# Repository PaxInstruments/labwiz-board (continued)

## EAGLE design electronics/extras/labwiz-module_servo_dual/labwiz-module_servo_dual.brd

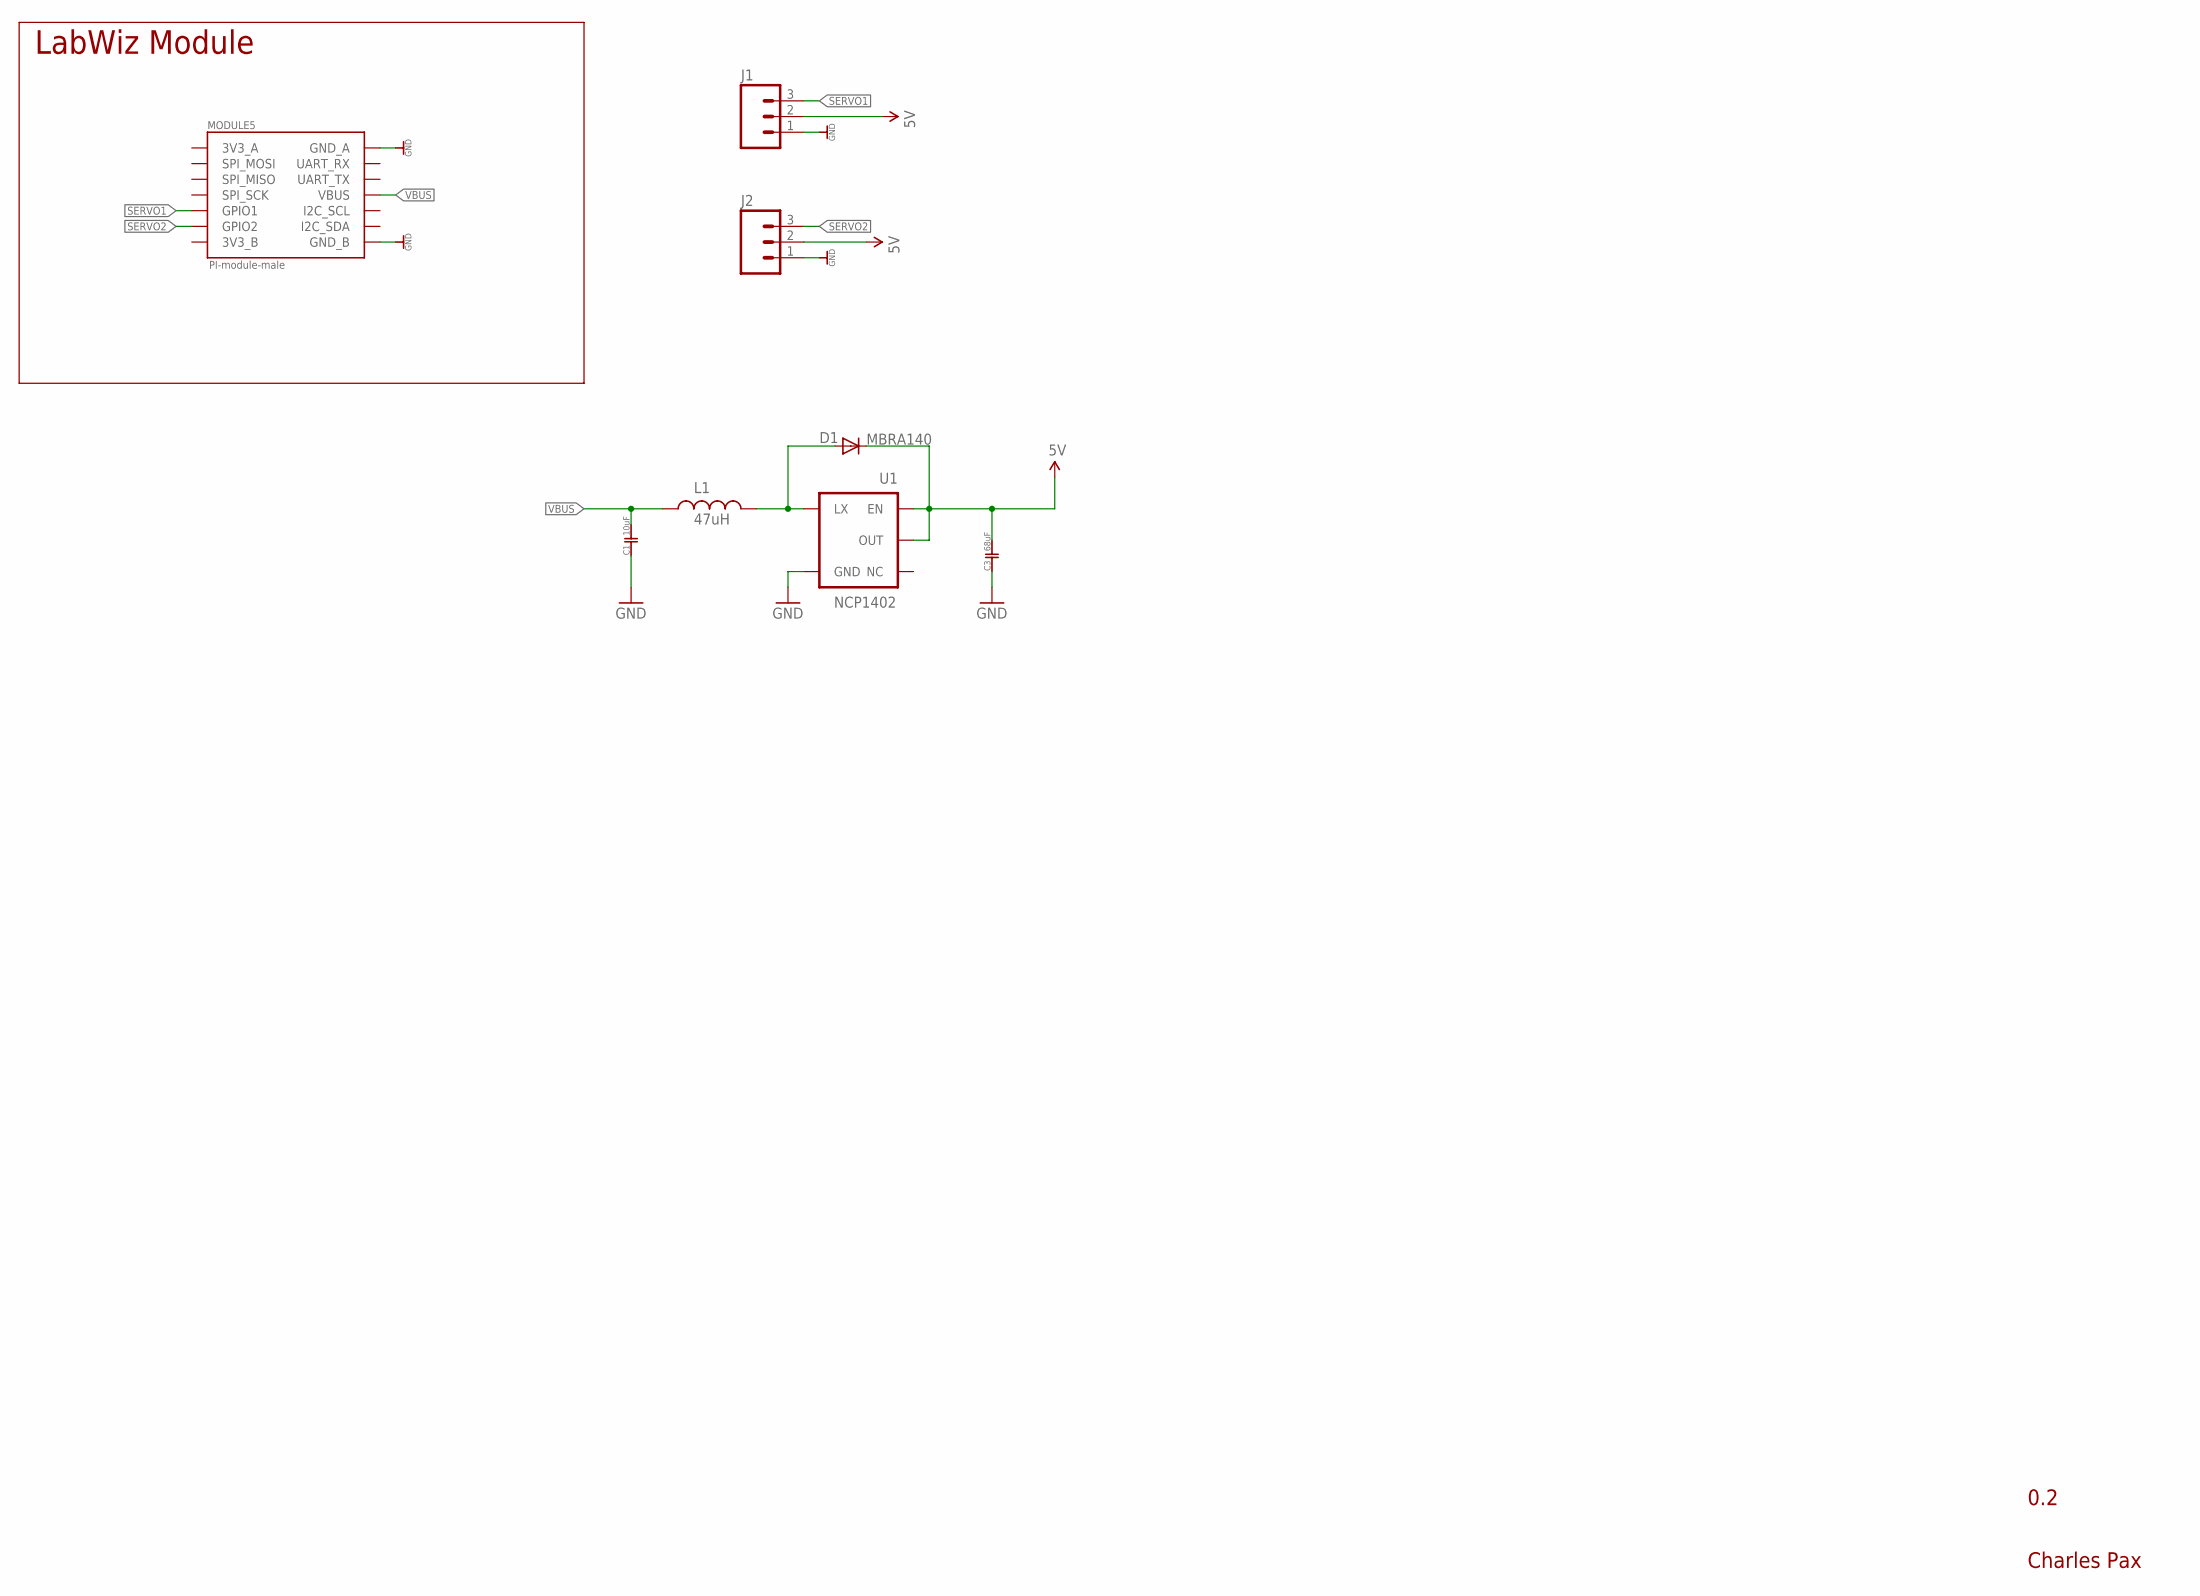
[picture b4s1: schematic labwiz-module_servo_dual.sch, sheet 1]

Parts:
C1: 10uF; 0603
C3: 68uF; 0603
D1: MBRA140; SMA-DIODE
J1, J2: M031X03_SMD_RA_MALE_POST_SMALLEST; 1X03_SMD_RA_MALE_POST_SMALLEST
L1: 47uH; CR54
MODULE5: PI-module-male; M07X2_2MM_EDGE
U1: NCP1402; SOT23-5

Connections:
3V3_A: MODULE5.P$13 (3V3_A)
5V: C3.2, D1.C, J1.2, J2.2, U1.1 (EN), U1.2 (OUT)
GND: C1.1, C3.1, J1.1, J2.1, MODULE5.P$2 (GND_B), MODULE5.P$14 (GND_A), U1.4 (GND)
unnamed: D1.A, L1.P$2 (2), U1.5 (LX)
SERVO1: J1.3, MODULE5.P$5 (GPIO1)
SERVO2: J2.3, MODULE5.P$3 (GPIO2)
VBUS: C1.2, L1.P$1 (1), MODULE5.P$8 (VBUS)

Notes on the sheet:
0.2
Charles Pax
LabWiz Module

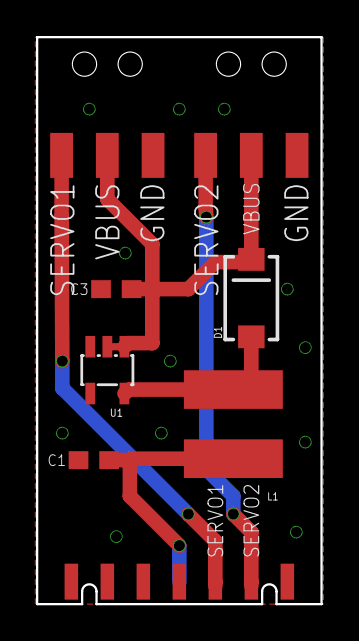
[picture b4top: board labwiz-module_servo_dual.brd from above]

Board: 4 copper layers, 15.8 x 31.5 mm, 8 parts (0 on the bottom side), 6 nets.

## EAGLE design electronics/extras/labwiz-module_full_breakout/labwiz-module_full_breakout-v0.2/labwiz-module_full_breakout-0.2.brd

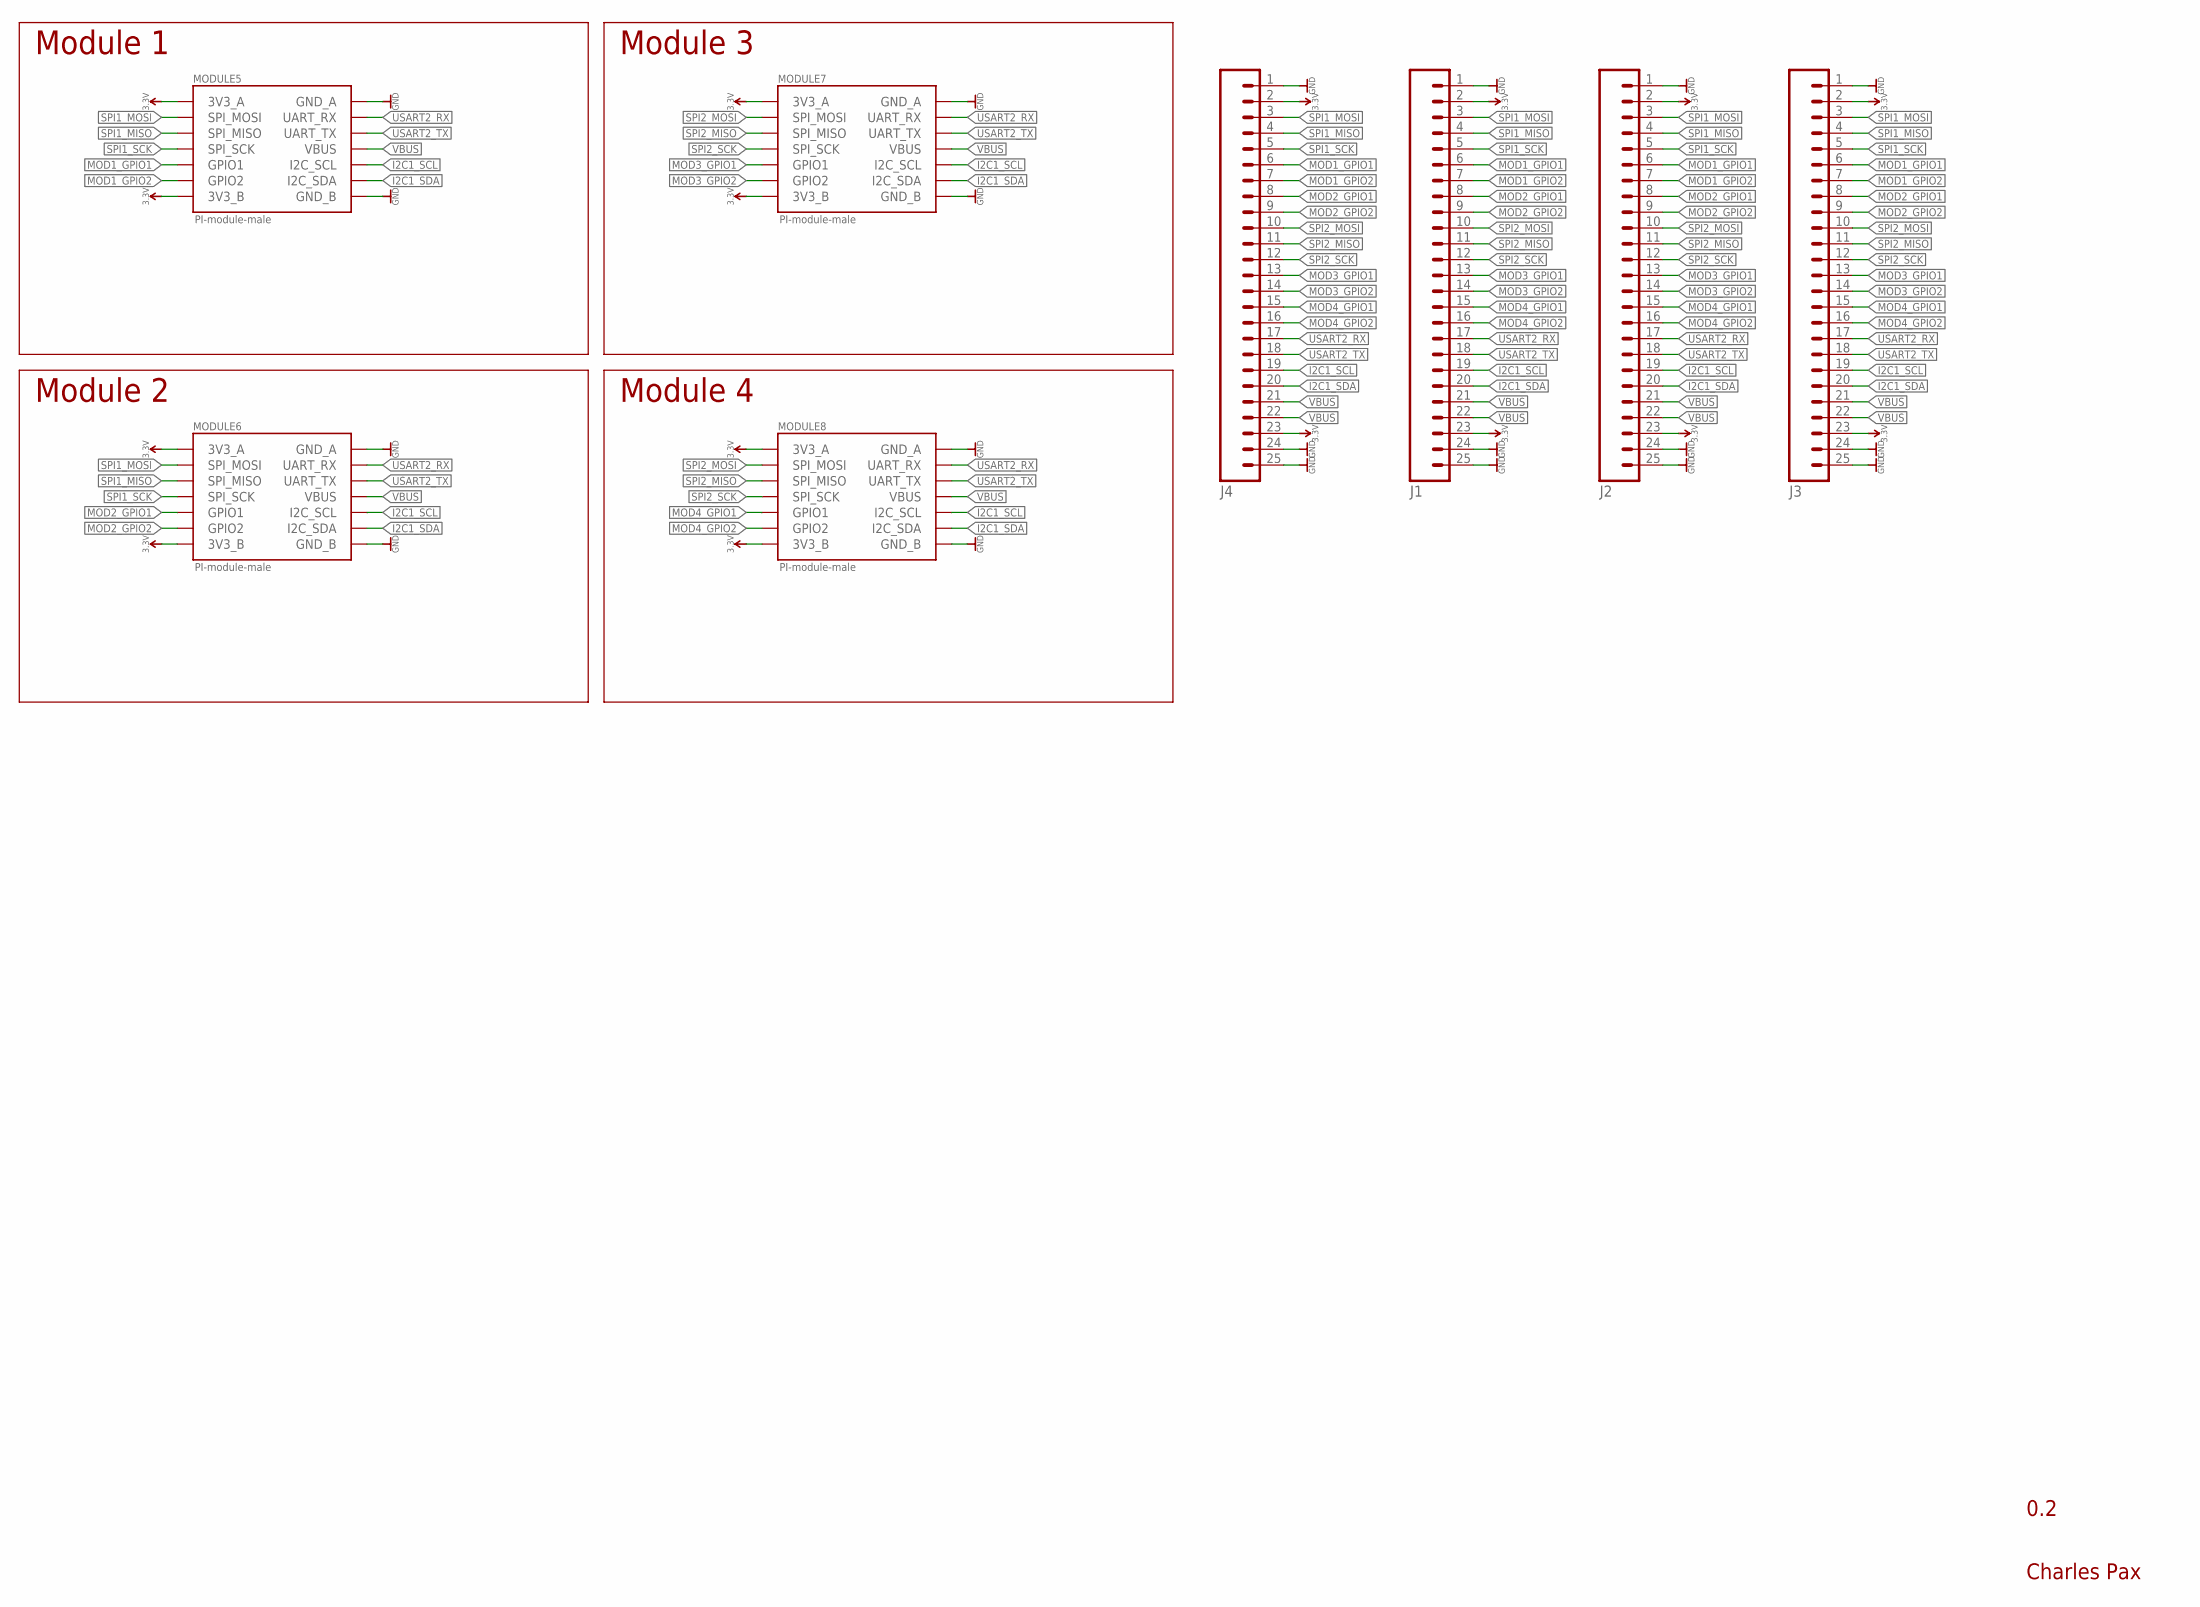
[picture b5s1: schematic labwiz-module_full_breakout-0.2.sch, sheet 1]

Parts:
J1, J2, J3, J4: M25PTH; 1X25
MODULE5, MODULE6, MODULE7, MODULE8: PI-module-male; M07X2_2MM_EDGE

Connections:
3.3V: J1.2, J1.23, J2.2, J2.23, J3.2, J3.23, J4.2, J4.23, MODULE5.P$1 (3V3_B), MODULE5.P$13 (3V3_A), MODULE6.P$1 (3V3_B), MODULE6.P$13 (3V3_A), MODULE7.P$1 (3V3_B), MODULE7.P$13 (3V3_A), MODULE8.P$1 (3V3_B), MODULE8.P$13 (3V3_A)
GND: J1.1, J1.24, J1.25, J2.1, J2.24, J2.25, J3.1, J3.24, J3.25, J4.1, J4.24, J4.25, MODULE5.P$2 (GND_B), MODULE5.P$14 (GND_A), MODULE6.P$2 (GND_B), MODULE6.P$14 (GND_A), MODULE7.P$2 (GND_B), MODULE7.P$14 (GND_A), MODULE8.P$2 (GND_B), MODULE8.P$14 (GND_A)
I2C1_SCL: J1.19, J2.19, J3.19, J4.19, MODULE5.P$6 (I2C_SCL), MODULE6.P$6 (I2C_SCL), MODULE7.P$6 (I2C_SCL), MODULE8.P$6 (I2C_SCL)
I2C1_SDA: J1.20, J2.20, J3.20, J4.20, MODULE5.P$4 (I2C_SDA), MODULE6.P$4 (I2C_SDA), MODULE7.P$4 (I2C_SDA), MODULE8.P$4 (I2C_SDA)
MOD1_GPIO1: J1.6, J2.6, J3.6, J4.6, MODULE5.P$5 (GPIO1)
MOD1_GPIO2: J1.7, J2.7, J3.7, J4.7, MODULE5.P$3 (GPIO2)
MOD2_GPIO1: J1.8, J2.8, J3.8, J4.8, MODULE6.P$5 (GPIO1)
MOD2_GPIO2: J1.9, J2.9, J3.9, J4.9, MODULE6.P$3 (GPIO2)
MOD3_GPIO1: J1.13, J2.13, J3.13, J4.13, MODULE7.P$5 (GPIO1)
MOD3_GPIO2: J1.14, J2.14, J3.14, J4.14, MODULE7.P$3 (GPIO2)
MOD4_GPIO1: J1.15, J2.15, J3.15, J4.15, MODULE8.P$5 (GPIO1)
MOD4_GPIO2: J1.16, J2.16, J3.16, J4.16, MODULE8.P$3 (GPIO2)
SPI1_MISO: J1.4, J2.4, J3.4, J4.4, MODULE5.P$9 (SPI_MISO), MODULE6.P$9 (SPI_MISO)
SPI1_MOSI: J1.3, J2.3, J3.3, J4.3, MODULE5.P$11 (SPI_MOSI), MODULE6.P$11 (SPI_MOSI)
SPI1_SCK: J1.5, J2.5, J3.5, J4.5, MODULE5.P$7 (SPI_SCK), MODULE6.P$7 (SPI_SCK)
SPI2_MISO: J1.11, J2.11, J3.11, J4.11, MODULE7.P$9 (SPI_MISO), MODULE8.P$9 (SPI_MISO)
SPI2_MOSI: J1.10, J2.10, J3.10, J4.10, MODULE7.P$11 (SPI_MOSI), MODULE8.P$11 (SPI_MOSI)
SPI2_SCK: J1.12, J2.12, J3.12, J4.12, MODULE7.P$7 (SPI_SCK), MODULE8.P$7 (SPI_SCK)
USART2_RX: J1.17, J2.17, J3.17, J4.17, MODULE5.P$12 (UART_RX), MODULE6.P$12 (UART_RX), MODULE7.P$12 (UART_RX), MODULE8.P$12 (UART_RX)
USART2_TX: J1.18, J2.18, J3.18, J4.18, MODULE5.P$10 (UART_TX), MODULE6.P$10 (UART_TX), MODULE7.P$10 (UART_TX), MODULE8.P$10 (UART_TX)
VBUS: J1.21, J1.22, J2.21, J2.22, J3.21, J3.22, J4.21, J4.22, MODULE5.P$8 (VBUS), MODULE6.P$8 (VBUS), MODULE7.P$8 (VBUS), MODULE8.P$8 (VBUS)

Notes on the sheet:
0.2
Charles Pax
Module 1
Module 2
Module 3
Module 4

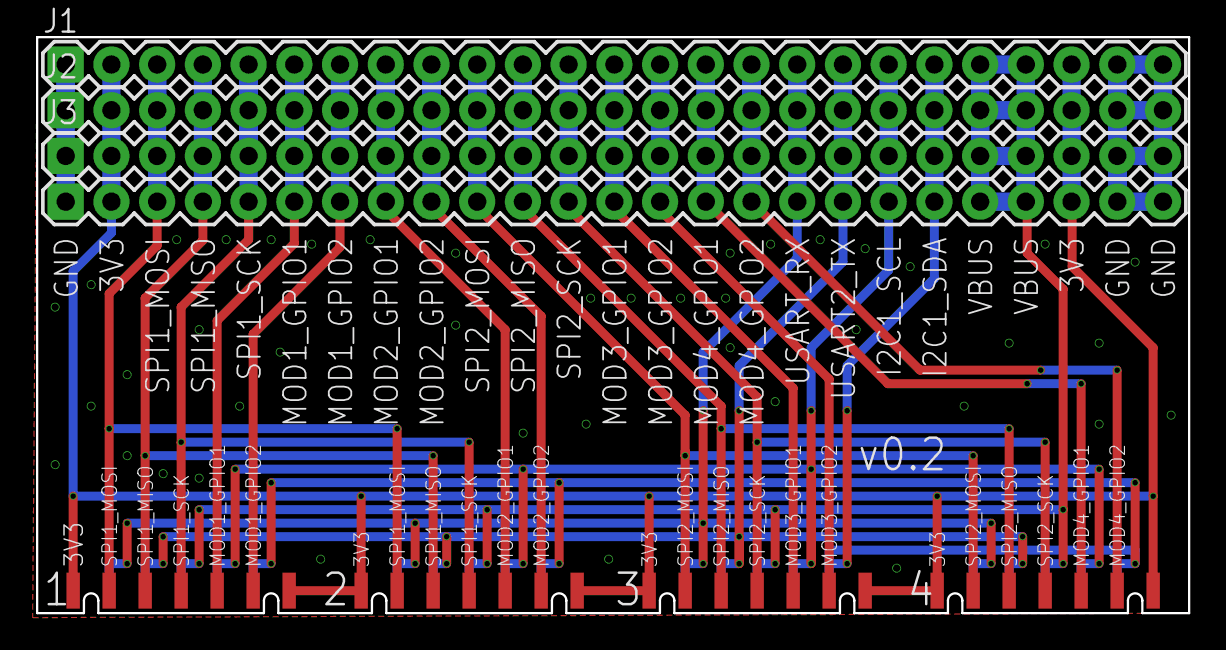
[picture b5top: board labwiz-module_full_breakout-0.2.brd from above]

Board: 4 copper layers, 64.0 x 32.0 mm, 8 parts (0 on the bottom side), 21 nets.

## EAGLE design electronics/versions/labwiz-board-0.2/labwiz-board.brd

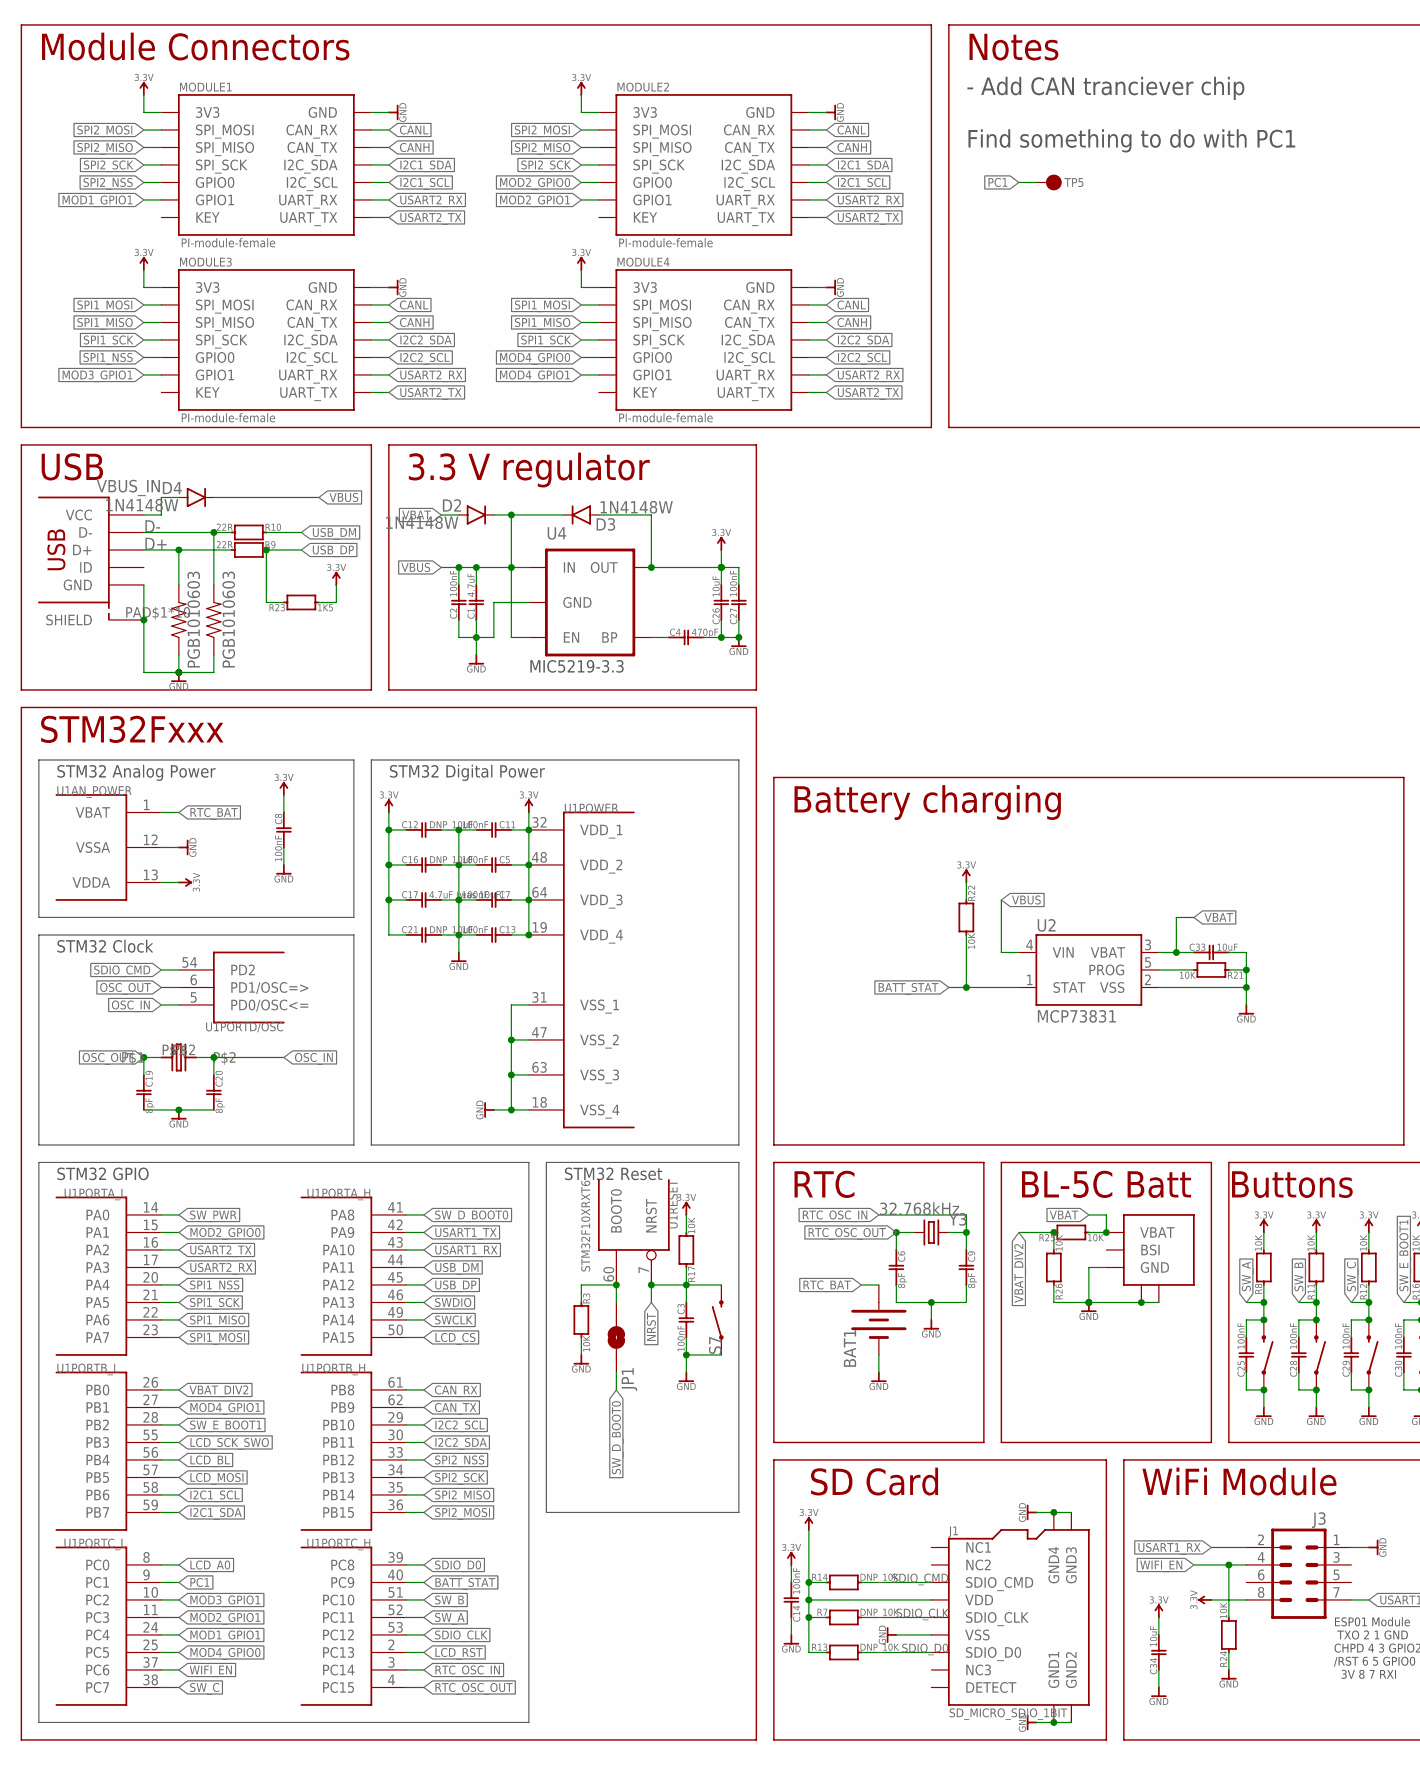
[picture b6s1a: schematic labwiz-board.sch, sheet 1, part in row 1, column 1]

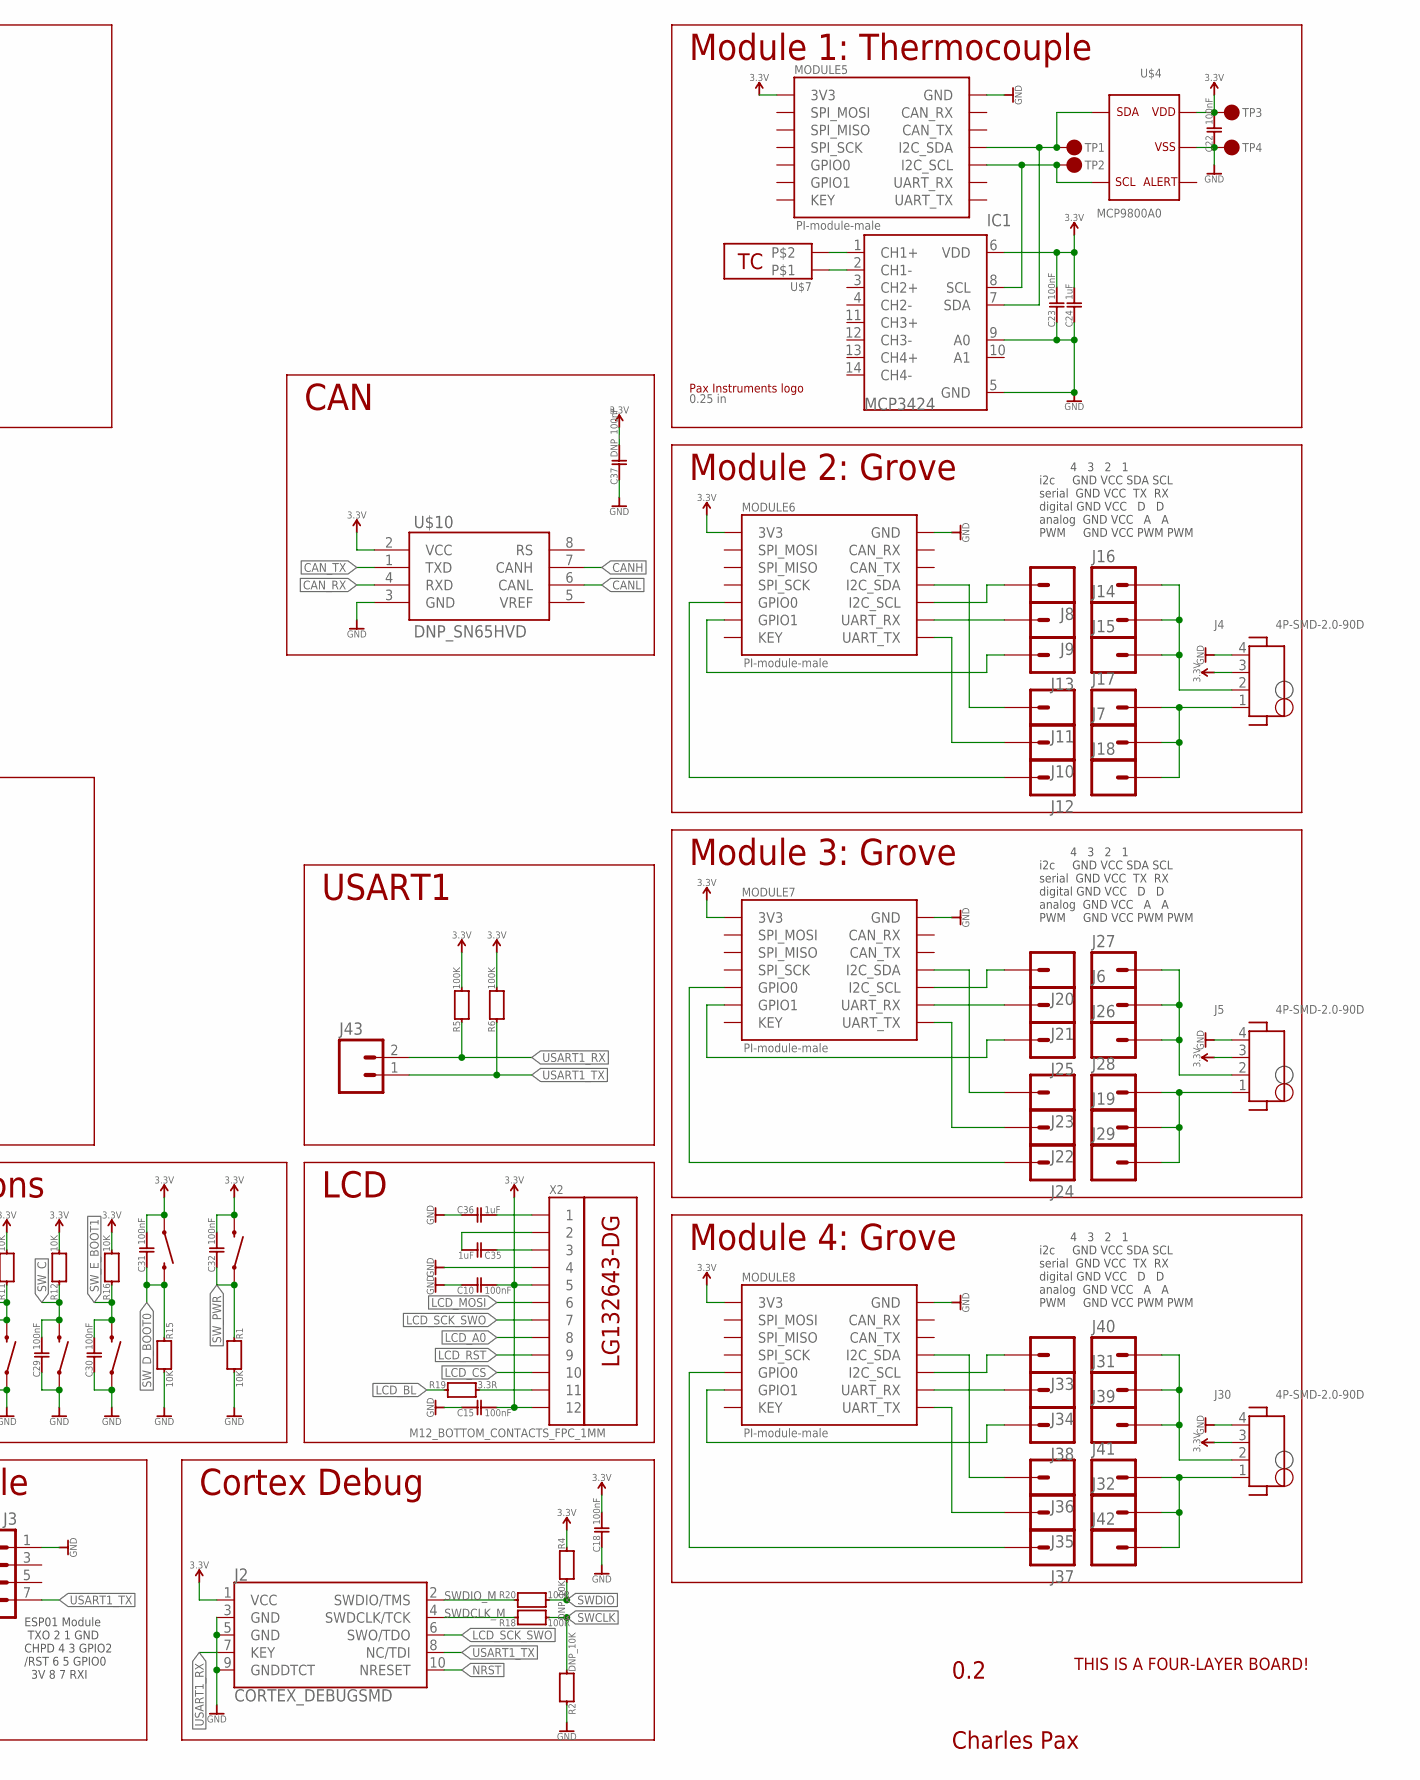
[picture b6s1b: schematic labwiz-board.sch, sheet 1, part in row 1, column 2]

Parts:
BAT1: BATTERY12MM; BATTCON_12MM
C1: 4.7uF; 0402
C2, C3, C5, C7, C8, C10, C11, C13, C14, C15, C18, C22, C23, C25, C27, C28, C29, C30, C31, C32: 100nF; 0402
C4: 470pF; 0402
C6, C9, C19, C20: 8pF; 0402
C12, C16, C21: DNP_10uF; 0402
C17: 4.7uF (was 10uF); 0402
C24, C35, C36: 1uF; 0402
C26, C33, C34: 10uF; 0402
C37: DNP_100nF; 0402
D2, D3, D4: 1N4148W; SOD-123
IC1: MCP3424; SO14
J1: SD_MICRO_SDIO_1BIT; SD_MICRO_1
J2: CORTEX_DEBUGSMD; SAMTECH_FTSH-105-01
J3: M04X2; 2X4
J4, J5, J30: 4P-SMD-2.0-90D; HW4-SMD-2.0-90D
J6, J7, J8, J9, J10, J11, J12, J13, J14, J15, J16, J17, J18, J19, J20, J21, J22, J23, J24, J25, J26, J27, J28, J29, J31, J32, J33, J34, J35, J36, J37, J38, J39, J40, J41, J42: M01SMD-4.5X1.5; PAD-1.5X4.5
J43: M02PTH; 1X02
JP1: JUMPER-PAD-2-NOYES_SILK; PAD-JUMPER-2-NO_YES_SILK
MODULE1, MODULE2, MODULE3, MODULE4: PI-module-female; M07X2_2MM_EDGE
MODULE5, MODULE6, MODULE7, MODULE8: PI-module-male; M07X2_2MM_EDGE
R1, R3, R8, R11, R12, R15, R16, R17, R21, R22, R24, R25, R26: 10K; 0402
R2, R4, R7, R13, R14: DNP_10K; 0402
R5, R6: 100K; 0402
R9, R10: 22R; R0402
R18, R20: 100R; 0402
R19: 3.3R; 0402
R23: 1K5; R0402
S1, S2, S3, S4, S5, S6: SWITCH-MOMENTARY-2SMD; TACTILE_SWITCH_SMD; MPN RS-187R05A2-DS MT RT
S7: SWITCH-MOMENTARY-2SMD-3; TACTILE_SWITCH_SMD-3
TP1, TP2, TP3, TP4: M01_TH
TP5: M01_PAD_1MM; PAD_1MM
U1: STM32F10XRXT6; TQFP64
U2: MCP73831; SOT23-5
U4: MIC5219-3.3V; SOT23-5; MPN MIC5219-3.3YM5 TR
U$1: USB_MICROSMT+THRUHULE; USB_MICRO_THRUHOLE; MPN 10118194-0001LF
U$2: FOUR_LAYER_WARNING
U$3: BL-5C-CONNECTOR
U$4: MCP9800A0; SOT23-5L
U$5: LG132643-DG; MPN LG132643-DW
U$7: THERMOCOUPLE_MINI_INSIDE; THERMOCOUPLE_CLIP_INSIDE
U$9: NX3225GD
U$10: DNP_SN65HVD; SO08
U$13: 0.25 in; PAX-LOGO-0.25IN
X2: M12_BOTTOM_CONTACTS_FPC_1MM; FPC_12P_1MM
Y3: 32.768kHz; CRYSTAL-SMD-3.2X1.5MM
Z1, Z2: PGB1010603; SPARKFUN-RESISTORS_0603-RES; MPN PGB1010603NRHF

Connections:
3.3V: C5.1, C7.1, C8.1, C10.2, C11.1, C12.1, C13.1, C14.2, C15.2, C16.1, C17.1, C18.2, C21.1, C26.2, C27.2, C31.2, C32.2, C34.2, C37.2, D3.A, J1.4 (VDD), J2.1 (VCC), J3.8, MODULE1.P$1 (3V3), MODULE2.P$1 (3V3), MODULE3.P$1 (3V3), MODULE4.P$1 (3V3), R4.2, R5.1, R6.1, R7.2, R8.1, R11.1, R12.1, R13.2, R14.2, R16.1, R17.1, R22.2, R23.1, S4.1, S6.3 (2), U1.13 (VDDA), U1.19 (VDD_4), U1.32 (VDD_1), U1.48 (VDD_2), U1.64 (VDD_3), U4.5 (OUT), U$10.2 (VCC), X2.5, X2.12
3.3V_1: C22.2, C23.2, C24.2, IC1.6 (VDD), MODULE5.P$13 (3V3), TP3.P$1, U$4.1
3.3V_2: J4.3 (2), MODULE6.P$13 (3V3)
3.3V_3: J5.3 (2), MODULE7.P$13 (3V3)
3.3V_4: J30.3 (2), MODULE8.P$13 (3V3)
BATT_STAT: R22.1, U1.40 (PC9), U2.1 (STAT)
BOOT0: JP1.2, R3.2, U1.60 (BOOT0)
CANH: MODULE1.P$6 (CAN_TX), MODULE2.P$6 (CAN_TX), MODULE3.P$6 (CAN_TX), MODULE4.P$6 (CAN_TX), U$10.7 (CANH)
CANL: MODULE1.P$4 (CAN_RX), MODULE2.P$4 (CAN_RX), MODULE3.P$4 (CAN_RX), MODULE4.P$4 (CAN_RX), U$10.6 (CANL)
CAN_RX: U1.61 (PB8), U$10.4 (RXD)
CAN_TX: U1.62 (PB9), U$10.1 (TXD)
D+: R9.1, U$1.PIN$3 (D+), Z1.2
D-: R10.1, U$1.PIN$2 (D-), Z2.2
GND: BAT1.GND (-), C1.1, C2.1, C3.2, C4.2, C5.2, C6.2, C7.2, C8.2, C9.2, C10.1, C11.2, C12.2, C13.2, C14.1, C15.1, C16.2, C17.2, C18.1, C19.2, C20.2, C21.2, C25.1, C26.1, C27.1, C28.1, C29.1, C30.1, C33.2, C34.1, C36.1, C37.1, J1.6 (VSS), J1.G1 (GND1), J1.G2 (GND2), J1.G3 (GND3), J1.G4 (GND4), J2.3 (GND), J2.5 (GND), J2.9 (GNDDTCT), J3.1, MODULE1.P$2 (GND), MODULE2.P$2 (GND), MODULE3.P$2 (GND), MODULE4.P$2 (GND), R1.1, R2.2, R3.1, R15.1, R21.2, R24.2, R26.2, S1.1, S2.1, S3.1, S5.1, S7.1, U1.12 (VSSA), U1.18 (VSS_4), U1.31 (VSS_1), U1.47 (VSS_2), U1.63 (VSS_3), U2.2 (VSS), U4.2 (GND), U$1.PAD$1 (SHIELD), U$1.PAD$2 (SHIELD), U$1.PAD$3 (SHIELD), U$1.PAD$4 (SHIELD), U$1.PAD$5 (SHIELD), U$1.PAD$6 (SHIELD), U$1.PAD$7 (SHIELD), U$1.PAD$8 (SHIELD), U$1.PAD$9 (SHIELD), U$1.PAD$10 (SHIELD), U$1.PIN$5 (GND), U$3.P$3 (GND), U$3.P$4, U$3.P$5, U$10.3 (GND), X2.4, Z1.1, Z2.1
GND_1: C22.1, C23.1, C24.1, IC1.5 (GND), IC1.9 (A0), MODULE5.P$14 (GND), TP4.P$1, U$4.2
GND_2: J4.4 (1), MODULE6.P$14 (GND)
GND_3: J5.4 (1), MODULE7.P$14 (GND)
GND_4: J30.4 (1), MODULE8.P$14 (GND)
I2C1_SCL: MODULE1.P$10 (I2C_SCL), MODULE2.P$10 (I2C_SCL), U1.58 (PB6)
I2C1_SDA: MODULE1.P$8 (I2C_SDA), MODULE2.P$8 (I2C_SDA), U1.59 (PB7)
I2C2_SCL: MODULE3.P$10 (I2C_SCL), MODULE4.P$10 (I2C_SCL), U1.29 (PB10)
I2C2_SDA: MODULE3.P$8 (I2C_SDA), MODULE4.P$8 (I2C_SDA), U1.30 (PB11)
LCD_A0: U1.8 (PC0), X2.8
LCD_BL: R19.2, U1.56 (PB4)
LCD_CS: U1.50 (PA15), X2.10
LCD_MOSI: U1.57 (PB5), X2.6
LCD_RST: U1.2 (PC13), X2.9
LCD_SCK_SWO: J2.6 (SWO/TDO), U1.55 (PB3), X2.7
MOD1_GPIO1: MODULE1.P$11 (GPIO1), U1.24 (PC4)
MOD2_GPIO0: MODULE2.P$9 (GPIO0), U1.15 (PA1)
MOD2_GPIO1: MODULE2.P$11 (GPIO1), U1.11 (PC3)
MOD3_GPIO1: MODULE3.P$11 (GPIO1), U1.10 (PC2)
MOD4_GPIO0: MODULE4.P$9 (GPIO0), U1.25 (PC5)
MOD4_GPIO1: MODULE4.P$11 (GPIO1), U1.27 (PB1)
unnamed: C4.1, U4.4 (BP)
unnamed: R19.1, X2.11
unnamed: J4.2 (3), J14.P$1, J15.P$1, J16.P$1
unnamed: J5.2 (3), J6.P$1, J26.P$1, J27.P$1
unnamed: IC1.2 (CH1-), U$7.P$1
unnamed: IC1.1 (CH1+), U$7.P$2
unnamed: C35.1, X2.3
unnamed: C35.2, X2.2
unnamed: C36.2, X2.1
unnamed: J4.1 (4), J7.P$1, J17.P$1, J18.P$1
unnamed: J5.1 (4), J19.P$1, J28.P$1, J29.P$1
unnamed: J20.P$1, MODULE7.P$6 (I2C_SCL)
unnamed: J21.P$1, MODULE7.P$4 (UART_RX)
unnamed: J8.P$1, MODULE6.P$6 (I2C_SCL)
unnamed: J9.P$1, MODULE6.P$4 (UART_RX)
unnamed: J10.P$1, MODULE6.P$2 (UART_TX)
unnamed: J11.P$1, MODULE6.P$8 (I2C_SDA)
unnamed: J13.P$1, MODULE6.P$3 (GPIO1)
unnamed: J12.P$1, MODULE6.P$5 (GPIO0)
unnamed: J22.P$1, MODULE7.P$2 (UART_TX)
unnamed: J23.P$1, MODULE7.P$8 (I2C_SDA)
unnamed: J25.P$1, MODULE7.P$3 (GPIO1)
unnamed: J24.P$1, MODULE7.P$5 (GPIO0)
unnamed: J30.2 (3), J31.P$1, J39.P$1, J40.P$1
unnamed: J30.1 (4), J32.P$1, J41.P$1, J42.P$1
unnamed: J33.P$1, MODULE8.P$6 (I2C_SCL)
unnamed: J34.P$1, MODULE8.P$4 (UART_RX)
unnamed: J35.P$1, MODULE8.P$2 (UART_TX)
unnamed: J36.P$1, MODULE8.P$8 (I2C_SDA)
unnamed: J38.P$1, MODULE8.P$3 (GPIO1)
unnamed: J37.P$1, MODULE8.P$5 (GPIO0)
unnamed: R21.1, U2.5 (PROG)
NRST: C3.1, J2.10 (NRESET), R17.2, S7.4 (2), U1.7 (NRST)
OSC_IN: C20.1, U1.5 (PD0/OSC<=), U$9.P$2
OSC_OUT: C19.1, U1.6 (PD1/OSC=>), U$9.P$1
PC1: TP5.P$1, U1.9 (PC1)
RTC_BAT: BAT1.PWR@1 (+), U1.1 (VBAT)
RTC_OSC_IN: C9.1, U1.3 (PC14), Y3.P$2 (2)
RTC_OSC_OUT: C6.1, U1.4 (PC15), Y3.P$1 (1)
SCL_1: IC1.8 (SCL), MODULE5.P$6 (I2C_SCL), TP2.P$1, U$4.4
SDA_1: IC1.7 (SDA), MODULE5.P$8 (I2C_SDA), TP1.P$1, U$4.5
SDIO_CLK: J1.5 (SDIO_CLK), R7.1, U1.53 (PC12)
SDIO_CMD: J1.3 (SDIO_CMD), R14.1, U1.54 (PD2)
SDIO_D0: J1.7 (SDIO_D0), R13.1, U1.39 (PC8)
SPI1_MISO: MODULE3.P$5 (SPI_MISO), MODULE4.P$5 (SPI_MISO), U1.22 (PA6)
SPI1_MOSI: MODULE3.P$3 (SPI_MOSI), MODULE4.P$3 (SPI_MOSI), U1.23 (PA7)
SPI1_NSS: MODULE3.P$9 (GPIO0), U1.20 (PA4)
SPI1_SCK: MODULE3.P$7 (SPI_SCK), MODULE4.P$7 (SPI_SCK), U1.21 (PA5)
SPI2_MISO: MODULE1.P$5 (SPI_MISO), MODULE2.P$5 (SPI_MISO), U1.35 (PB14)
SPI2_MOSI: MODULE1.P$3 (SPI_MOSI), MODULE2.P$3 (SPI_MOSI), U1.36 (PB15)
SPI2_NSS: MODULE1.P$9 (GPIO0), U1.33 (PB12)
SPI2_SCK: MODULE1.P$7 (SPI_SCK), MODULE2.P$7 (SPI_SCK), U1.34 (PB13)
SWCLK: R2.1, R18.1, U1.49 (PA14)
SWDCLK_M: J2.4 (SWDCLK/TCK), R18.2
SWDIO: R4.1, R20.1, U1.46 (PA13)
SWDIO_M: J2.2 (SWDIO/TMS), R20.2
SW_A: C25.2, R8.2, S3.3 (2), U1.52 (PC11)
SW_B: C28.2, R11.2, S2.3 (2), U1.51 (PC10)
SW_C: C29.2, R12.2, S1.3 (2), U1.38 (PC7)
SW_D_BOOT0: C31.1, JP1.1, R15.2, S4.3 (2), U1.41 (PA8)
SW_E_BOOT1: C30.2, R16.2, S5.3 (2), U1.28 (PB2)
SW_PWR: C32.1, R1.2, S6.1, U1.14 (PA0)
USART1_RX: J2.7 (KEY), J3.2, J43.2, R5.2, U1.43 (PA10)
USART1_TX: J2.8 (NC/TDI), J3.7, J43.1, R6.2, U1.42 (PA9)
USART2_RX: MODULE1.P$12 (UART_RX), MODULE2.P$12 (UART_RX), MODULE3.P$12 (UART_RX), MODULE4.P$12 (UART_RX), U1.17 (PA3)
USART2_TX: MODULE1.P$14 (UART_TX), MODULE2.P$14 (UART_TX), MODULE3.P$14 (UART_TX), MODULE4.P$14 (UART_TX), U1.16 (PA2)
USB_DM: R10.2, U1.44 (PA11)
USB_DP: R9.2, R23.2, U1.45 (PA12)
VBAT: C33.1, D2.A, R25.1, U2.3 (VBAT), U$3.P$1 (VBAT)
VBAT_DIV2: R25.2, R26.1, U1.26 (PB0)
VBUS: C1.2, C2.2, D2.C, D3.C, D4.C, U2.4 (VIN), U4.1 (IN), U4.3 (EN)
VBUS_IN: D4.A, U$1.PIN$1 (VCC)
WIFI_EN: J3.4, R24.1, U1.37 (PC6)

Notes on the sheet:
MIC5219-3.3
USB
3.3 V regulator
LCD
Buttons
0.2
Charles Pax
SD Card
STM32 Digital Power
STM32 Analog Power
STM32 Clock
STM32 Reset
STM32Fxxx
STM32 GPIO
RTC
Module Connectors
BL-5C Batt
Cortex Debug
Module 1: Thermocouple
Module 2: Grove
- Add CAN tranciever chip
ESP01 Module TXO 2 1 GND CHPD 4 3 GPIO2 /RST 6 5 GPIO0 3V 8 7 RXI
WiFi Module
4 3 2 1 i2c GND VCC SDA SCL serial GND VCC TX RX digital GND VCC D D analog GND VCC A A PWM GND VCC PWM PWM
Module 3: Grove
Module 4: Grove
Battery charging
USART1
Notes
Find something to do with PC1
CAN

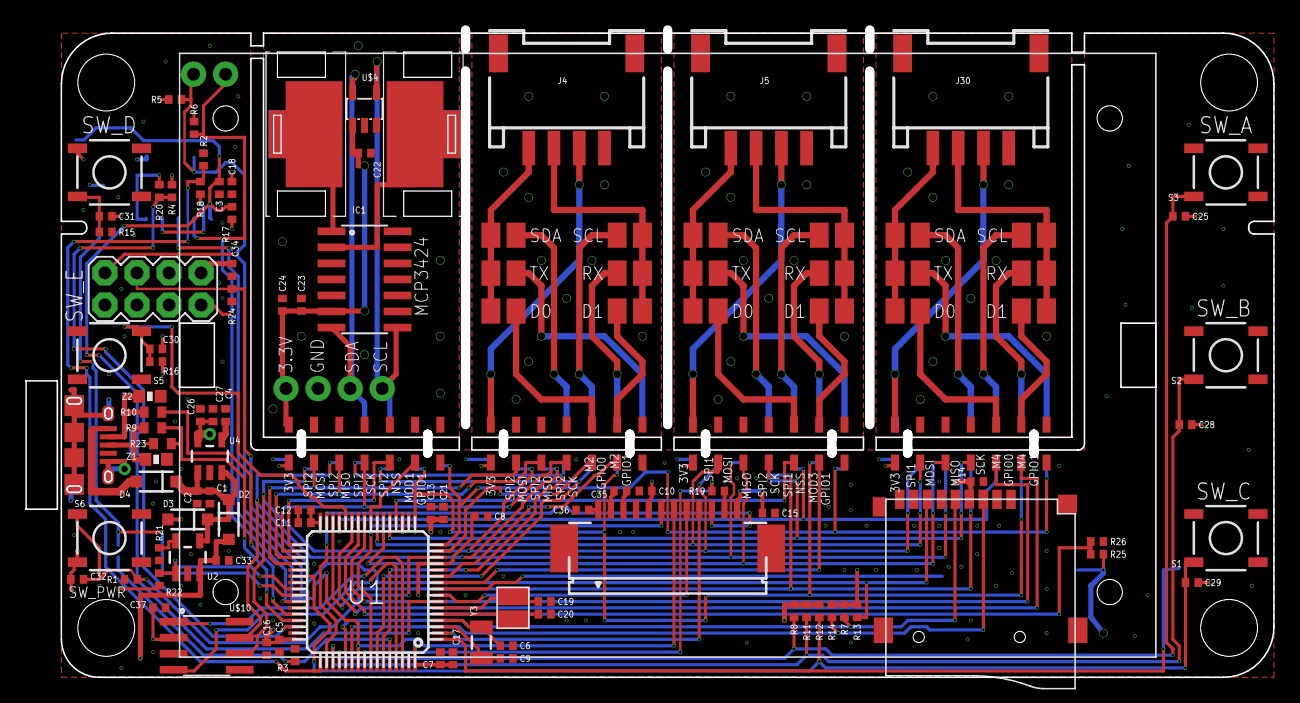
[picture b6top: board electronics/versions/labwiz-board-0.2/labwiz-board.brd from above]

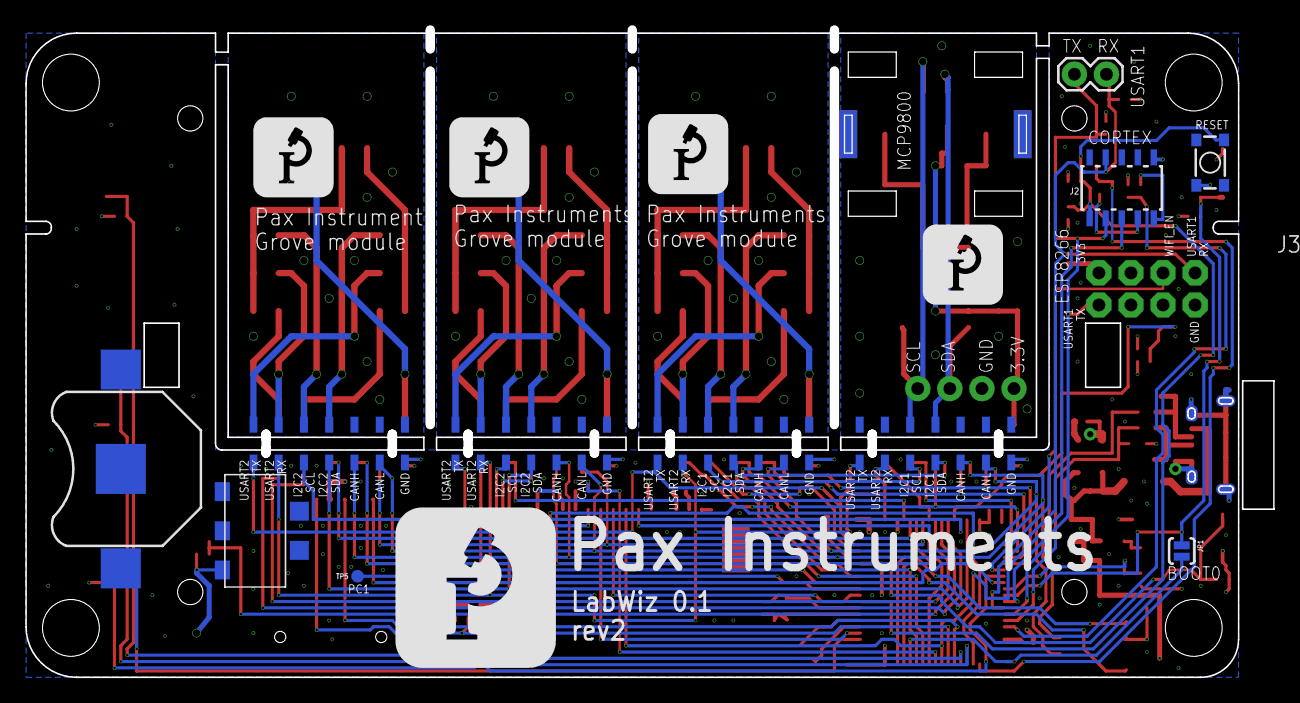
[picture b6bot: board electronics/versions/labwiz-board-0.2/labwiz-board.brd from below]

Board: 4 copper layers, 98.8 x 51.2 mm, 152 parts (13 on the bottom side), 107 nets.

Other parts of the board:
U$6: PAX-LOGO-0.5IN
U$8, U$11, U$12: 0.25 in; PAX-LOGO-0.25IN
